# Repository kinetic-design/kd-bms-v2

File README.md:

# kd-bms-v2
Battery Monitoring System Version 2.0 for 192 cells
Designed by Steve Schulz
Kicad V5.1.6 
LTC6804-2 based

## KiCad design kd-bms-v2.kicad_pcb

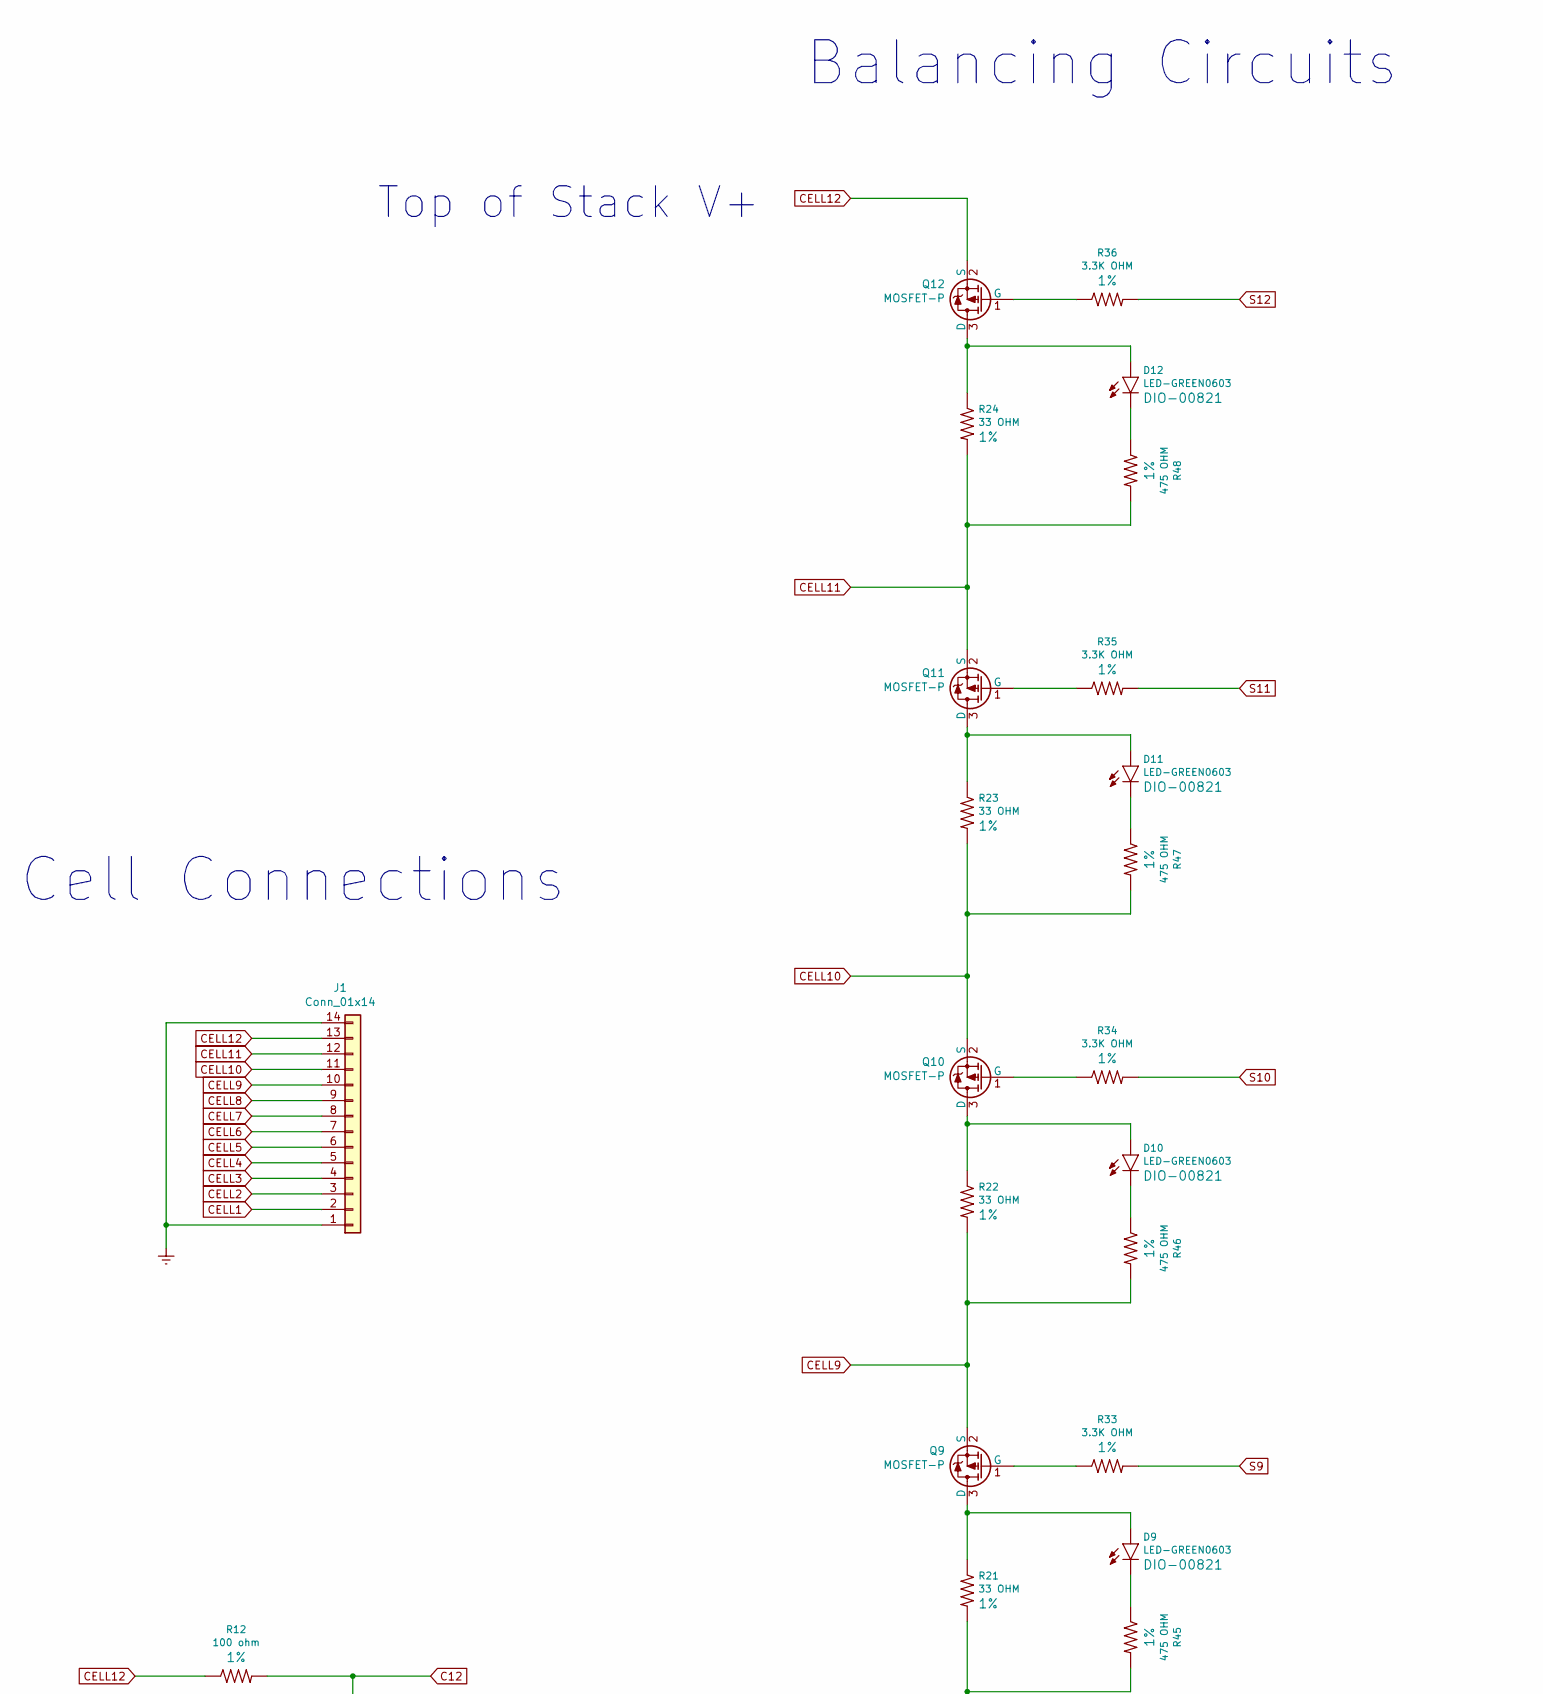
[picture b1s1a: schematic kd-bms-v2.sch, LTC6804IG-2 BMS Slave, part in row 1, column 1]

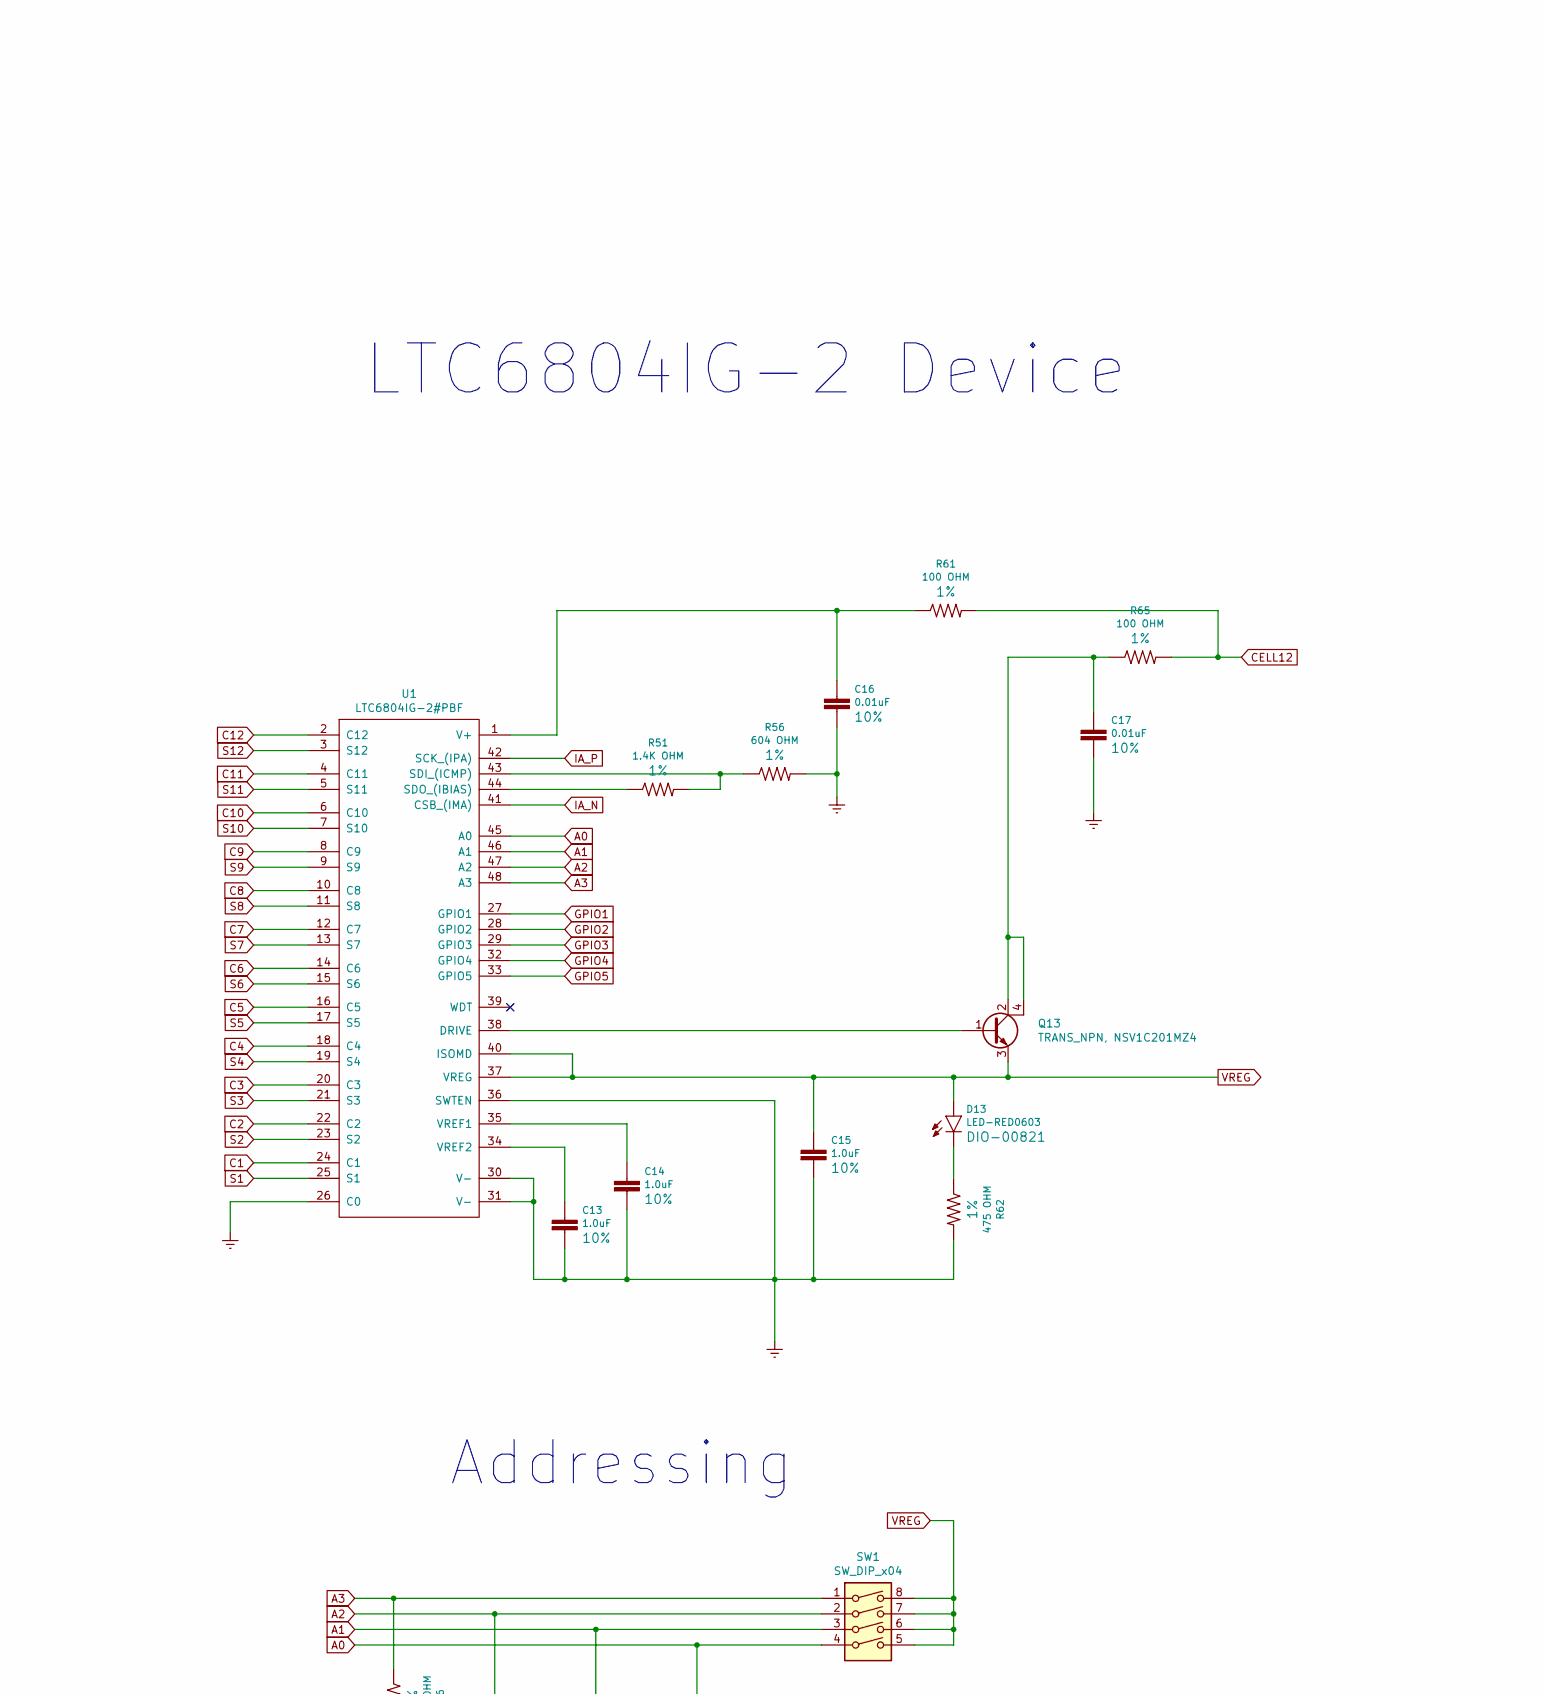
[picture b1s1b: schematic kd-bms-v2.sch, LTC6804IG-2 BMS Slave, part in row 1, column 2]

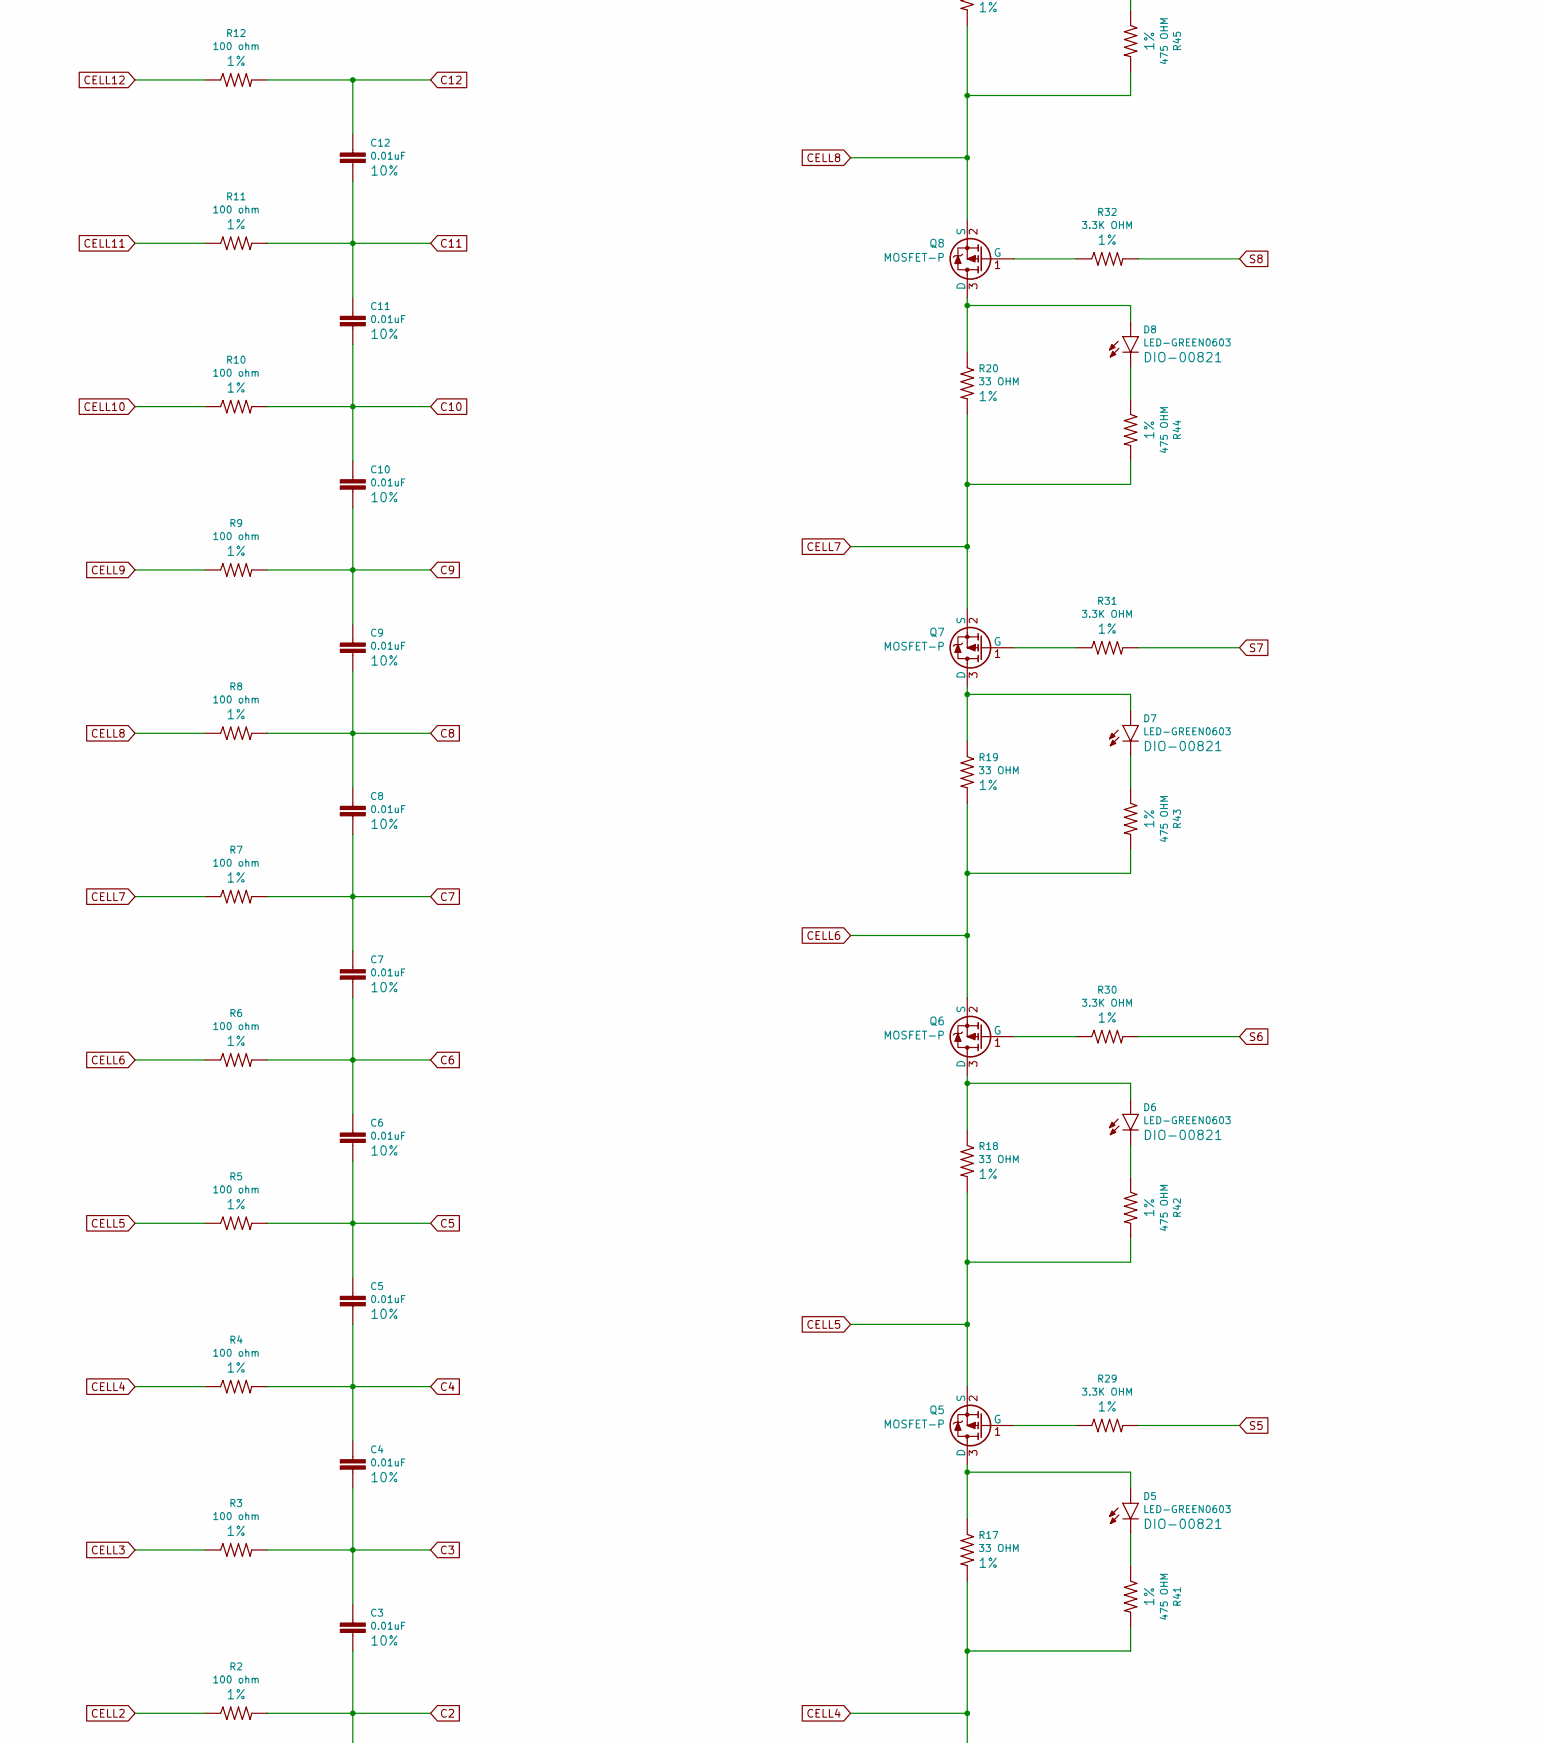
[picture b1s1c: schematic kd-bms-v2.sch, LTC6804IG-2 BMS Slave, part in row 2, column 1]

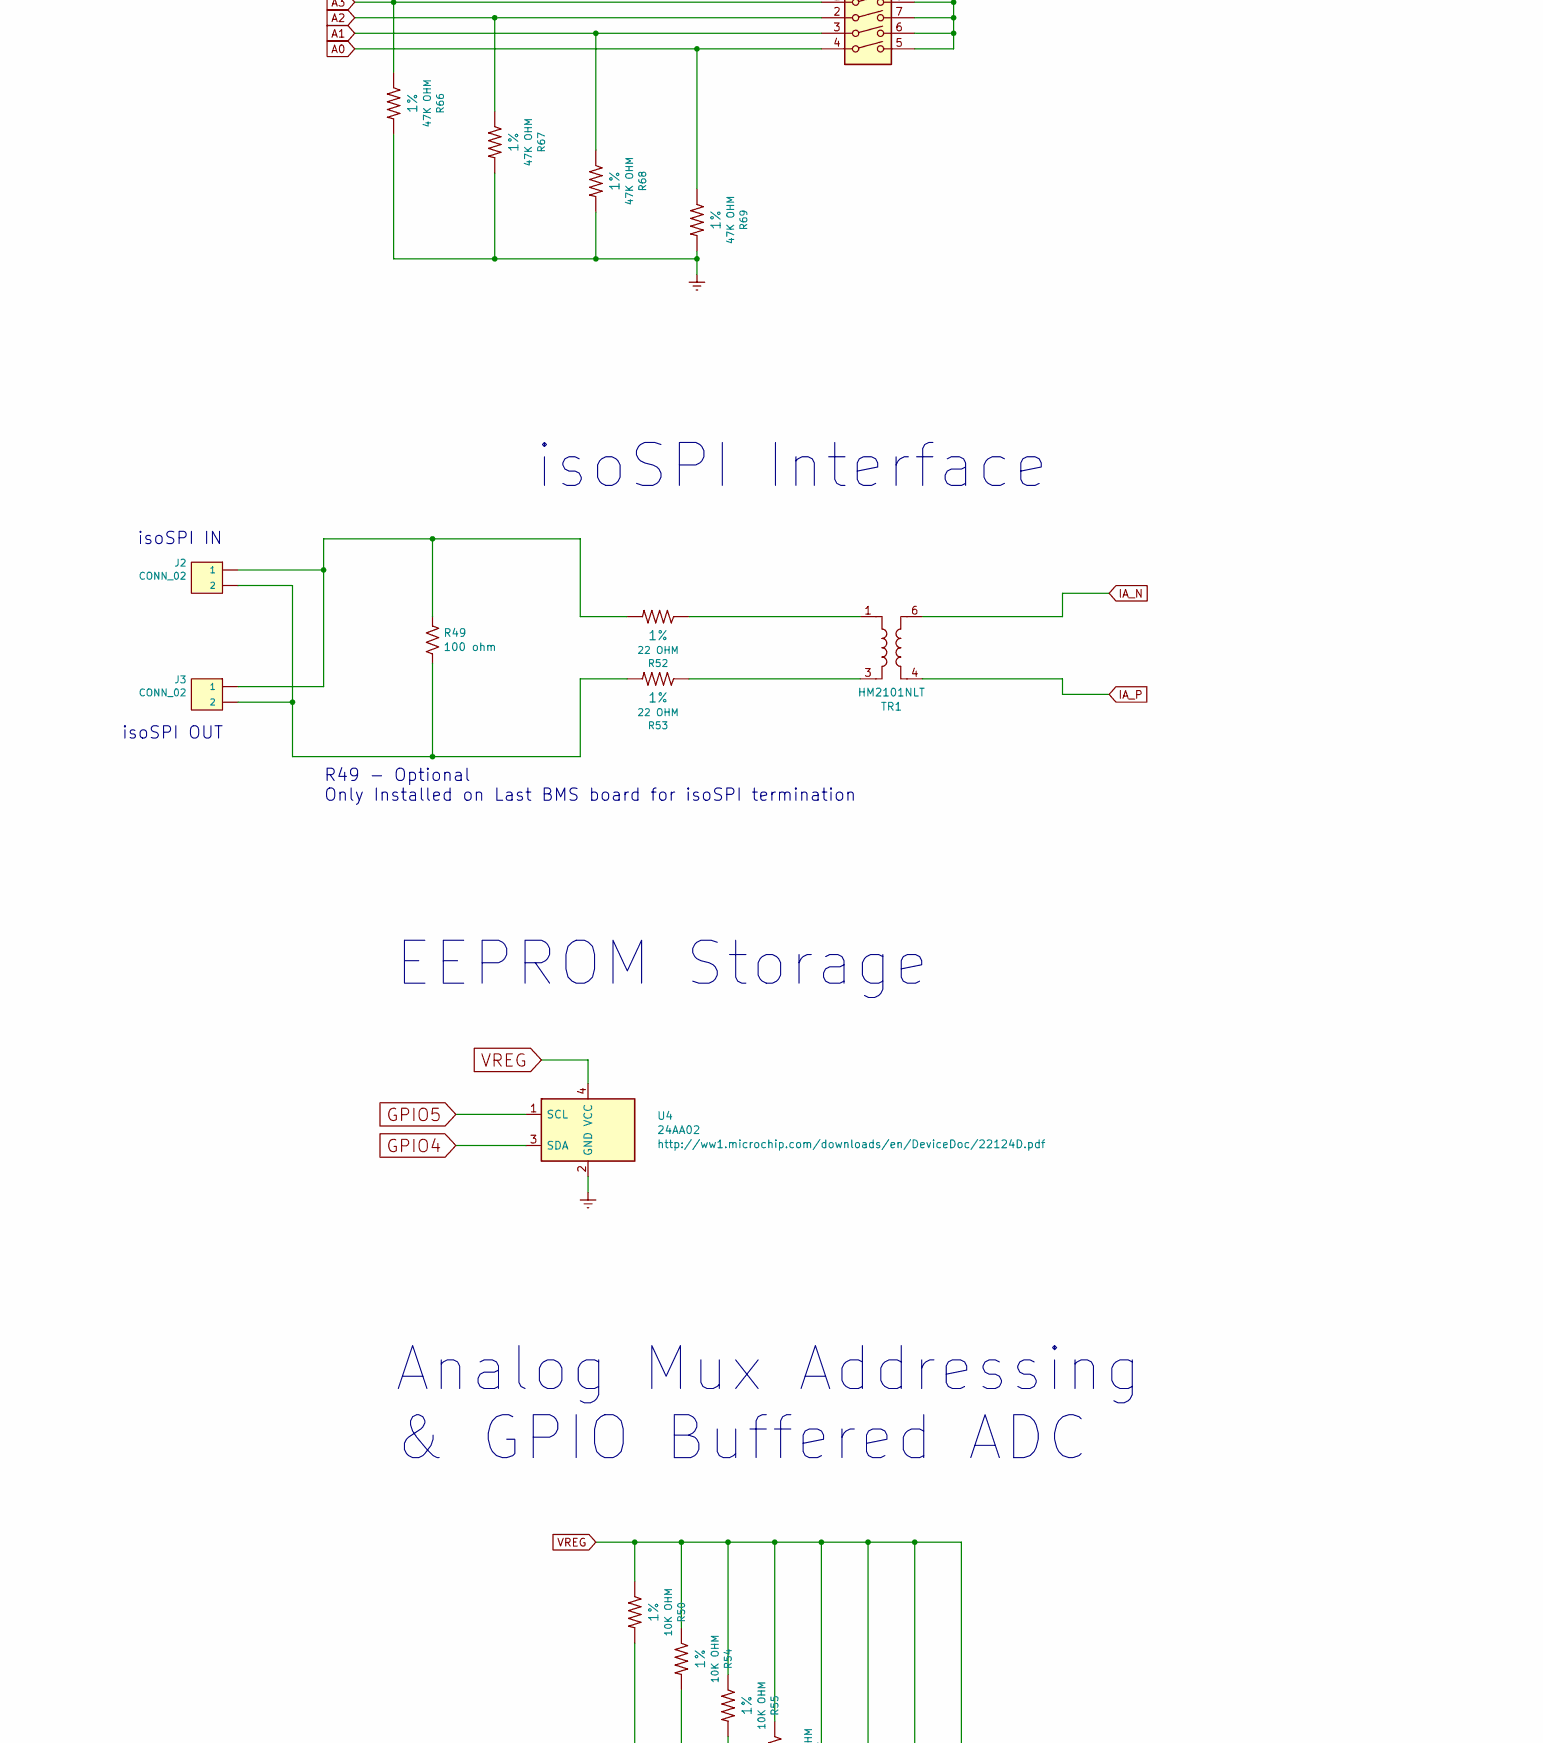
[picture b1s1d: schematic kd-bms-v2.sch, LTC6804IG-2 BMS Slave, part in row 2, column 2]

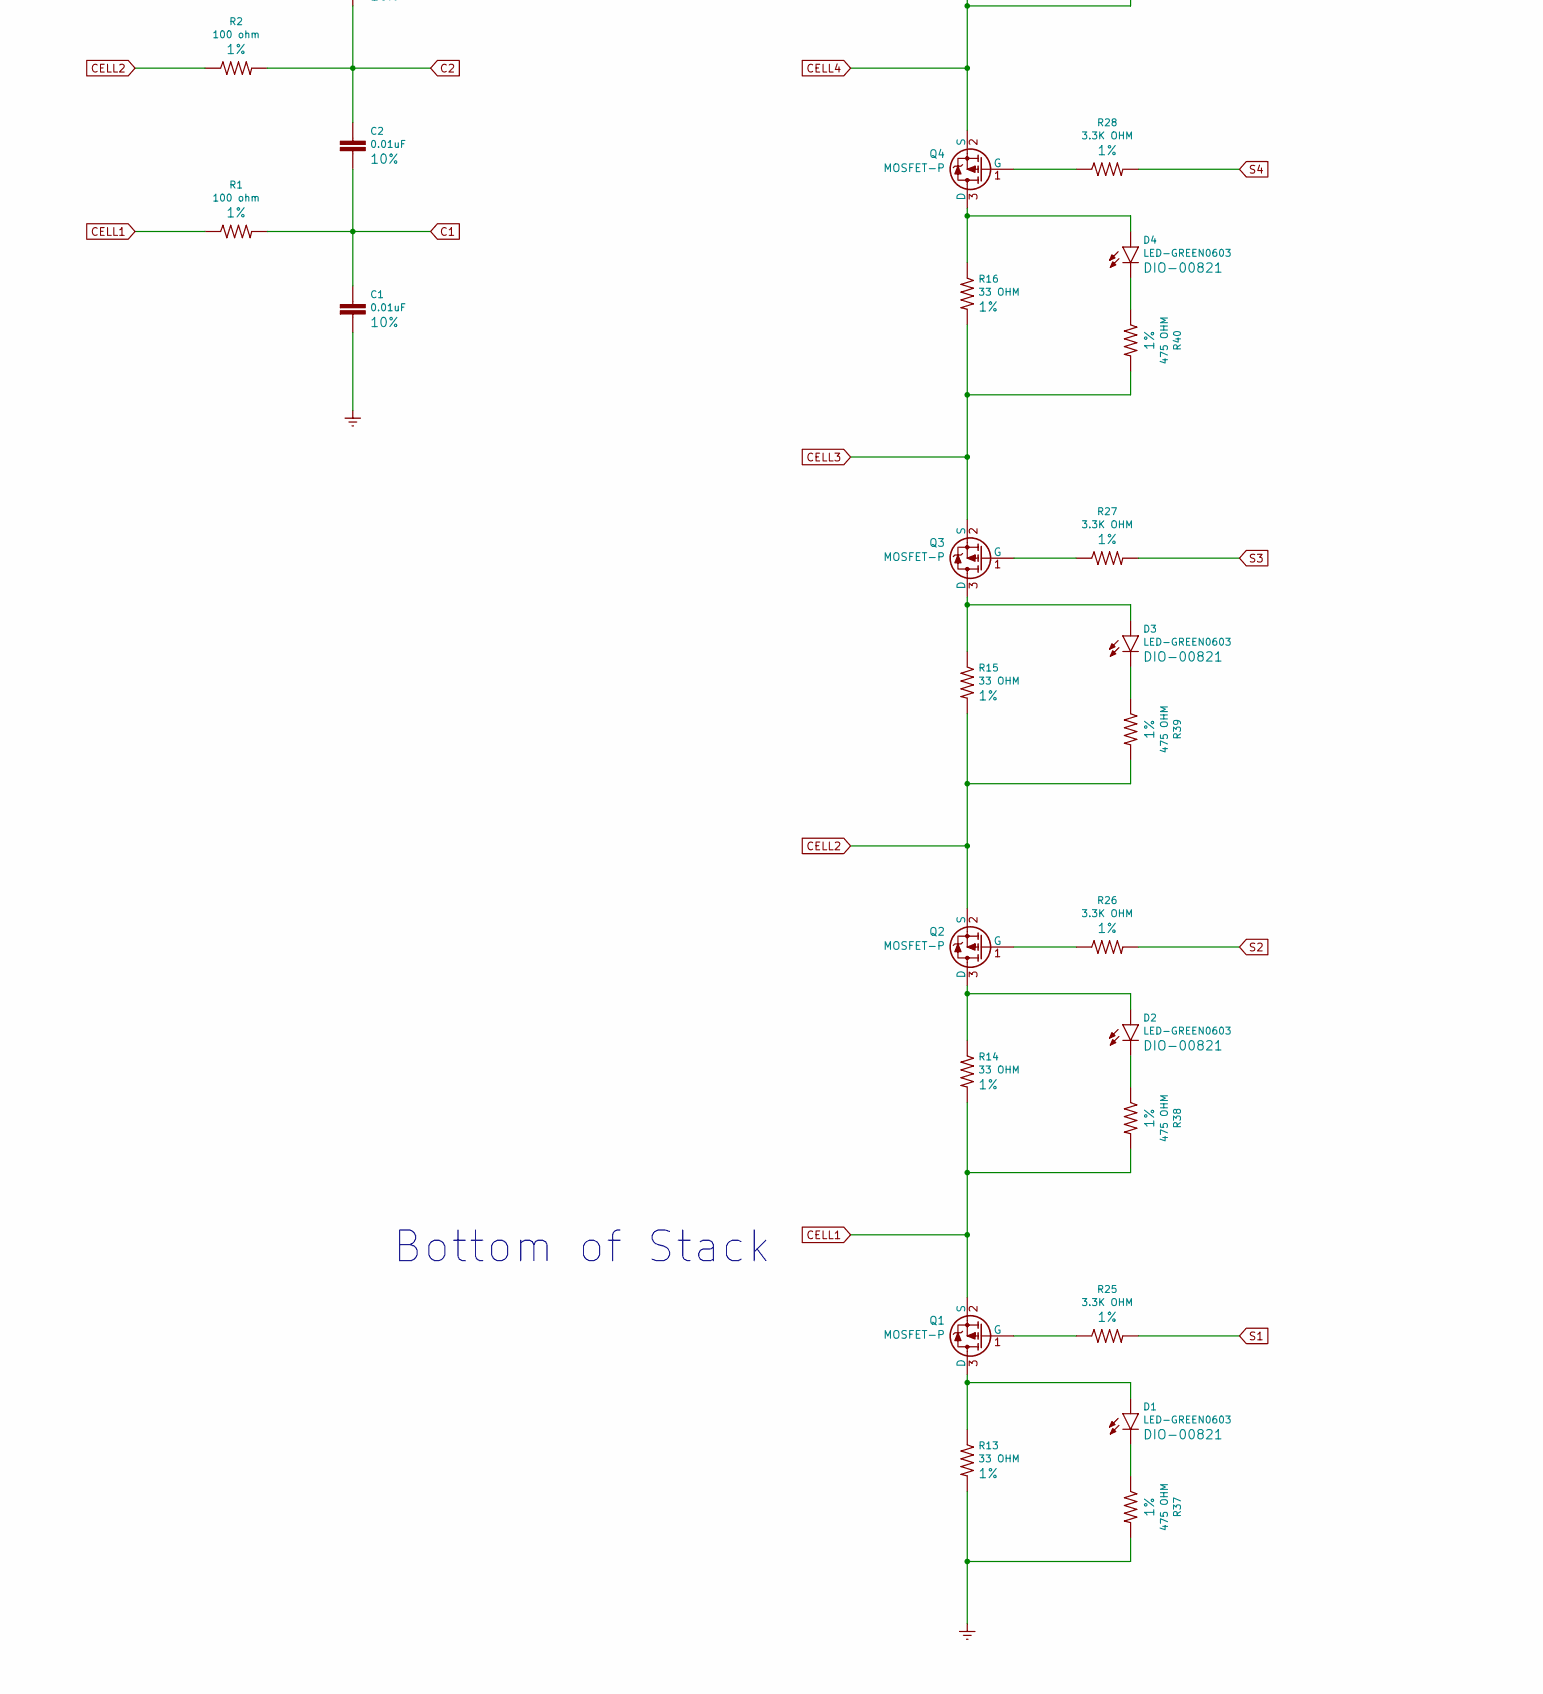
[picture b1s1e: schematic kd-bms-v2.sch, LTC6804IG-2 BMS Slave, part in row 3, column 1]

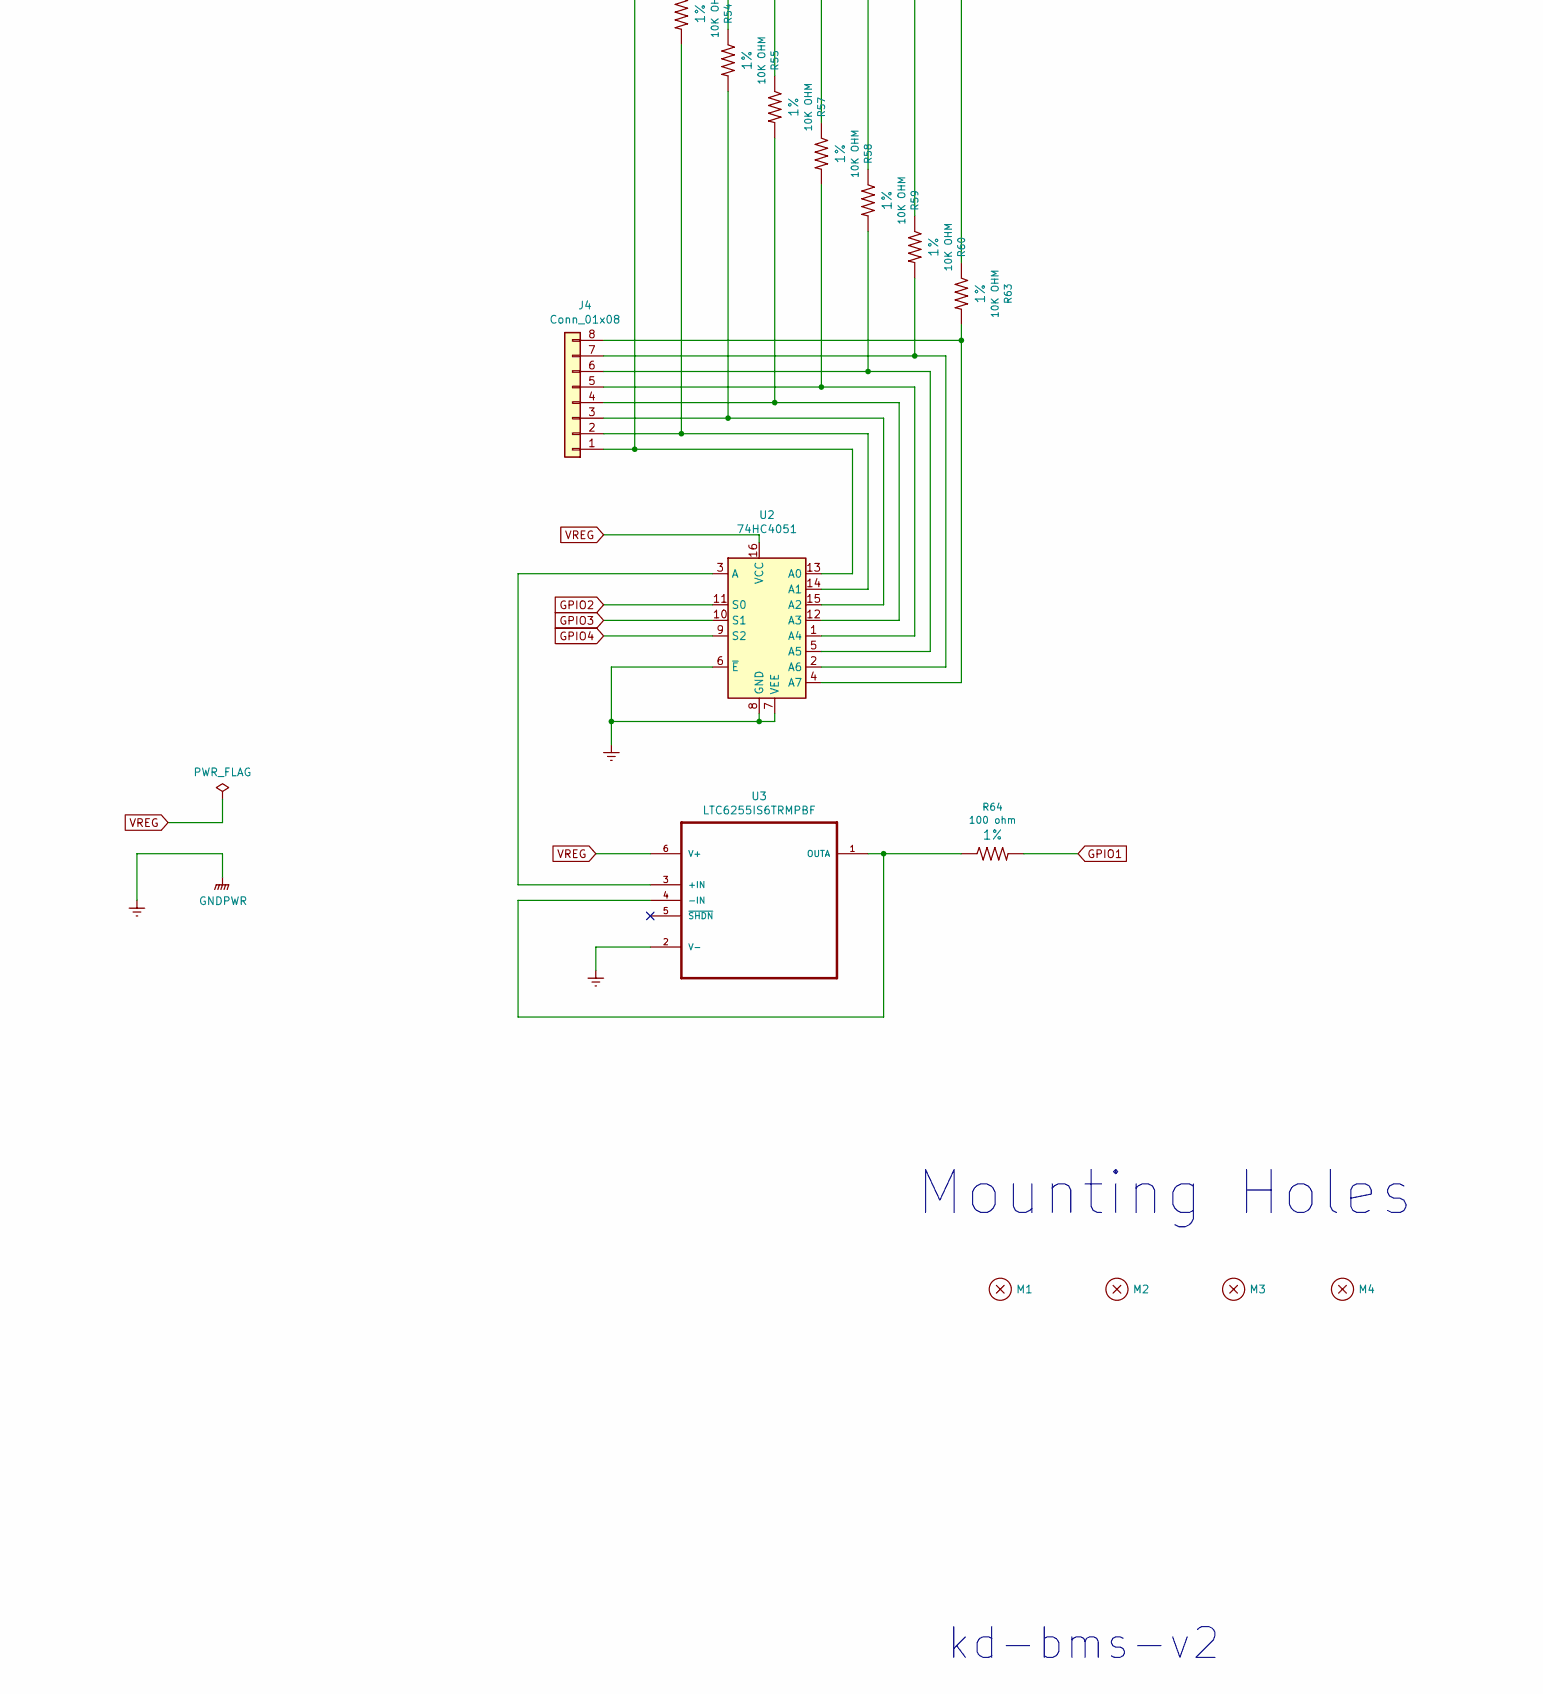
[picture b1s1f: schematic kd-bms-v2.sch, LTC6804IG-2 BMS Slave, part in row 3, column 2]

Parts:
C1, C2, C3, C4, C5, C6, C7, C8, C9, C10, C11, C12: 0.01uF; 0603; Tolerance 10%; Voltage 50V
C13, C14, C15: 1.0uF; 0805; Tolerance 10%; Voltage 100V
C16, C17: 0.01uF; 0805; Tolerance 10%; Voltage 100V
D1, D2, D3, D4, D5, D6, D7, D8, D9, D10, D11, D12: LED-GREEN0603; LED-0603; Tolerance DIO-00821; Voltage 5v
D13: LED-RED0603; LED-0603; Tolerance DIO-00821; Voltage 5v
J1: Conn_01x14; 1X14; Tolerance NA; Voltage 100V
J2, J3: CONN_02; 1X02
J4: Conn_01x08; 1X08; Tolerance NA; Voltage 100V
M1, M2, M3, M4: MOUNT_HOLE; STAND-OFF
Q1, Q2, Q3, Q4, Q5, Q6, Q7, Q8, Q9, Q10, Q11, Q12: MOSFET-P; SOT23-3; Tolerance unipolar; Voltage -30V
Q13: TRANS_NPN, NSV1C201MZ4; SOT-223; Tolerance automotive; Voltage 100V
R1, R2, R3, R4, R5, R6, R7, R8, R9, R10, R11, R12, R64: 100 ohm; 0603; Tolerance 1%; Voltage 50V
R13, R14, R15, R16, R17, R18, R19, R20, R21, R22, R23, R24: 33 OHM; R_2512_6332Metric; Tolerance 1%; Voltage High
R25, R26, R27, R28, R29, R30, R31, R32, R33, R34, R35, R36: 3.3K OHM; 0603; Tolerance 1%; Voltage 50V
R37, R38, R39, R40, R41, R42, R43, R44, R45, R46, R47, R48, R62: 475 OHM; 0603; Tolerance 1%; Voltage 50V
R49: 100 ohm; R_0805_HandSoldering
R50, R54, R55, R57, R58, R59, R60, R63: 10K OHM; 0603; Tolerance 1%; Voltage 50V
R51: 1.4K OHM; 0603; Tolerance 1%; Voltage 50V
R52, R53: 22 OHM; 0603; Tolerance 1%; Voltage 50V
R56: 604 OHM; 0603; Tolerance 1%; Voltage 50V
R61, R65: 100 OHM; 0603; Tolerance 1%; Voltage 50V
R66, R67, R68, R69: 47K OHM; 0603; Tolerance 1%; Voltage 50V
SW1: SW_DIP_x04; DIPSWITCH-04-SMD; Tolerance 1000 cycles; Voltage 24VDC
TR1: HM2101NLT; Tolerance 2500V; Voltage 1000Vrms
U1: LTC6804IG-2#PBF; SOP50P780X200-48N
U2: 74HC4051; TSSOP16; Tolerance MIL-PRF-38535; Voltage 2v to 6v
U3: LTC6255IS6TRMPBF; SOT95P280X100-6N; Tolerance RRIO Op Amps; Voltage 1.8V to 5.25V
U4: 24AA02; SOT23-5; Tolerance Automotive; Voltage 1.8v to 5.5v

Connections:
A0: R69.1, SW1.4, U1.45 (A0)
A1: R68.1, SW1.3, U1.46 (A1)
A2: R67.1, SW1.2, U1.47 (A2)
A3: R66.1, SW1.1, U1.48 (A3)
C1: C1.1, C2.2, R1.2, U1.24 (C1)
C2: C2.1, C3.2, R2.2, U1.22 (C2)
C3: C3.1, C4.2, R3.2, U1.20 (C3)
C4: C4.1, C5.2, R4.2, U1.18 (C4)
C5: C5.1, C6.2, R5.2, U1.16 (C5)
C6: C6.1, C7.2, R6.2, U1.14 (C6)
C7: C7.1, C8.2, R7.2, U1.12 (C7)
C8: C8.1, C9.2, R8.2, U1.10 (C8)
C9: C9.1, C10.2, R9.2, U1.8 (C9)
C10: C10.1, C11.2, R10.2, U1.6 (C10)
C11: C11.1, C12.2, R11.2, U1.4 (C11)
C12: C12.1, R12.2, U1.2 (C12)
CELL1: J1.2, Q1.2 (S), R1.1, R14.2, R38.2
CELL2: J1.3, Q2.2 (S), R2.1, R15.2, R39.2
CELL3: J1.4, Q3.2 (S), R3.1, R16.2, R40.2
CELL4: J1.5, Q4.2 (S), R4.1, R17.2, R41.2
CELL5: J1.6, Q5.2 (S), R5.1, R18.2, R42.2
CELL6: J1.7, Q6.2 (S), R6.1, R19.2, R43.2
CELL7: J1.8, Q7.2 (S), R7.1, R20.2, R44.2
CELL8: J1.9, Q8.2 (S), R8.1, R21.2, R45.2
CELL9: J1.10, Q9.2 (S), R9.1, R22.2, R46.2
CELL10: J1.11, Q10.2 (S), R10.1, R23.2, R47.2
CELL11: J1.12, Q11.2 (S), R11.1, R24.2, R48.2
CELL12: J1.13, Q12.2 (S), R12.1, R61.2, R65.2
GND: C1.2, C13.2, C14.2, C15.2, C16.2, C17.2, J1.1, J1.14, R13.2, R37.2, R56.2, R62.2, R66.2, R67.2, R68.2, R69.2, U1.26 (C0), U1.30 (V-), U1.31 (V-), U1.36 (SWTEN), U2.6 (~E), U2.7 (VEE), U2.8 (GND), U3.2 (V-), U4.2 (GND)
GPIO1: R64.2, U1.27 (GPIO1)
GPIO2: U1.28 (GPIO2), U2.11 (S0)
GPIO3: U1.29 (GPIO3), U2.10 (S1)
GPIO4: U1.32 (GPIO4), U2.9 (S2), U4.3 (SDA)
GPIO5: U1.33 (GPIO5), U4.1 (SCL)
IA_N: TR1.6, U1.41 (CSB_(IMA))
IA_P: TR1.4, U1.42 (SCK_(IPA))
unnamed: C13.1, U1.34 (VREF2)
unnamed: C14.1, U1.35 (VREF1)
unnamed: C16.1, R61.1, U1.1 (V+)
unnamed: C17.1, Q13.2 (C), Q13.4 (C), R65.1
unnamed: D1.A, Q1.3 (D), R13.1
unnamed: D1.C, R37.1
unnamed: D2.A, Q2.3 (D), R14.1
unnamed: D2.C, R38.1
unnamed: D3.A, Q3.3 (D), R15.1
unnamed: D3.C, R39.1
unnamed: D4.A, Q4.3 (D), R16.1
unnamed: D4.C, R40.1
unnamed: D5.A, Q5.3 (D), R17.1
unnamed: D5.C, R41.1
unnamed: D6.A, Q6.3 (D), R18.1
unnamed: D6.C, R42.1
unnamed: D7.A, Q7.3 (D), R19.1
unnamed: D7.C, R43.1
unnamed: D8.A, Q8.3 (D), R20.1
unnamed: D8.C, R44.1
unnamed: D9.A, Q9.3 (D), R21.1
unnamed: D9.C, R45.1
unnamed: D10.A, Q10.3 (D), R22.1
unnamed: D10.C, R46.1
unnamed: D11.A, Q11.3 (D), R23.1
unnamed: D11.C, R47.1
unnamed: D12.A, Q12.3 (D), R24.1
unnamed: D12.C, R48.1
unnamed: D13.C, R62.1
unnamed: J2.1, J3.1, R49.1, R52.2
unnamed: J2.2, J3.2, R49.2, R53.2
unnamed: J4.1, R50.2, U2.13 (A0)
unnamed: J4.2, R54.2, U2.14 (A1)
unnamed: J4.3, R55.2, U2.15 (A2)
unnamed: J4.4, R57.2, U2.12 (A3)
unnamed: J4.5, R58.2, U2.1 (A4)
unnamed: J4.6, R59.2, U2.5 (A5)
unnamed: J4.7, R60.2, U2.2 (A6)
unnamed: J4.8, R63.2, U2.4 (A7)
unnamed: Q1.1 (G), R25.1
unnamed: Q2.1 (G), R26.1
unnamed: Q3.1 (G), R27.1
unnamed: Q4.1 (G), R28.1
unnamed: Q5.1 (G), R29.1
unnamed: Q6.1 (G), R30.1
unnamed: Q7.1 (G), R31.1
unnamed: Q8.1 (G), R32.1
unnamed: Q9.1 (G), R33.1
unnamed: Q10.1 (G), R34.1
unnamed: Q11.1 (G), R35.1
unnamed: Q12.1 (G), R36.1
unnamed: Q13.1 (B), U1.38 (DRIVE)
unnamed: R51.1, U1.44 (SDO_(IBIAS))
unnamed: R51.2, R56.1, U1.43 (SDI_(ICMP))
unnamed: R52.1, TR1.1
unnamed: R53.1, TR1.3
unnamed: R64.1, U3.1 (OUTA), U3.4 (-IN)
unnamed: U2.3 (A), U3.3 (+IN)
S1: R25.2, U1.25 (S1)
S2: R26.2, U1.23 (S2)
S3: R27.2, U1.21 (S3)
S4: R28.2, U1.19 (S4)
S5: R29.2, U1.17 (S5)
S6: R30.2, U1.15 (S6)
S7: R31.2, U1.13 (S7)
S8: R32.2, U1.11 (S8)
S9: R33.2, U1.9 (S9)
S10: R34.2, U1.7 (S10)
S11: R35.2, U1.5 (S11)
S12: R36.2, U1.3 (S12)
VREG: C15.1, D13.A, Q13.3 (E), R50.1, R54.1, R55.1, R57.1, R58.1, R59.1, R60.1, R63.1, SW1.5, SW1.6, SW1.7, SW1.8, U1.37 (VREG), U1.40 (ISOMD), U2.16 (VCC), U3.6 (V+), U4.4 (VCC)

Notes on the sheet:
Addressing
kd-bms-v2
isoSPI Interface
Analog Mux Addressing & GPIO Buffered ADC
LTC6804IG-2 Device
Cell Connections
Balancing Circuits
Mounting Holes
Top of Stack V+
Bottom of Stack
isoSPI OUT
isoSPI IN
EEPROM Storage
R49 - Optional Only Installed on Last BMS board for isoSPI termination

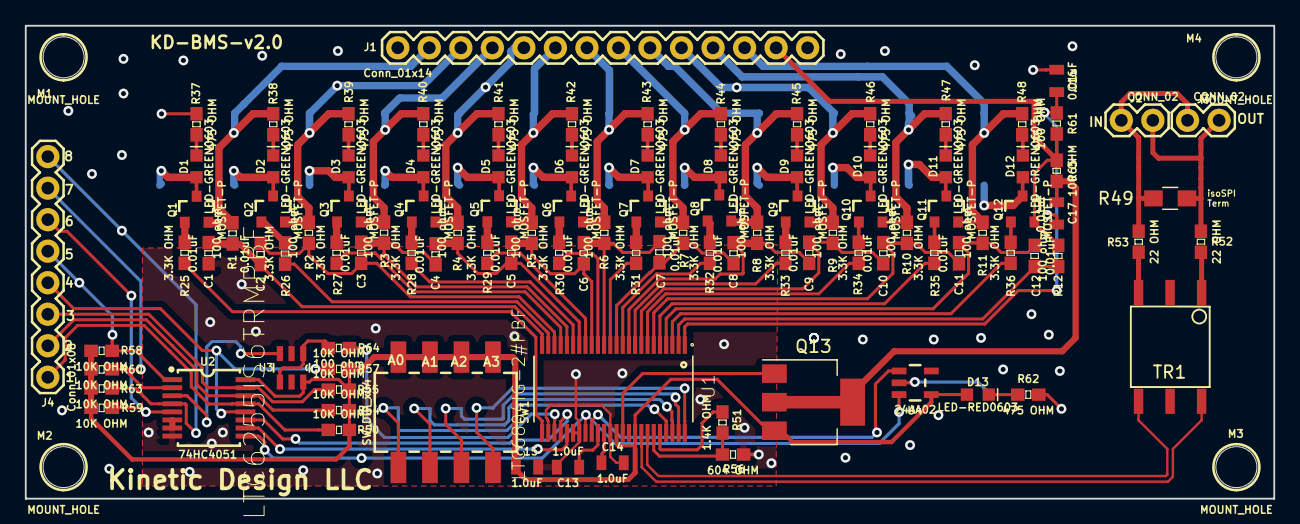
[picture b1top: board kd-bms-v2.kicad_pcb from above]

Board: 4 copper layers, 100.6 x 38.1 mm, 126 parts (0 on the bottom side), 107 nets.

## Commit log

2020-07-24 Add files via upload
    Kinetic Design Battery Management System V2.0 tested to 192 cells LG
